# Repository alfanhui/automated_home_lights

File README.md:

# automated_home_lights
An arduino project to control 3 relay mains switches when entering a room. Controls for current ambient light, detection of direction of travel by a PIR sensor and a door magnet switch.

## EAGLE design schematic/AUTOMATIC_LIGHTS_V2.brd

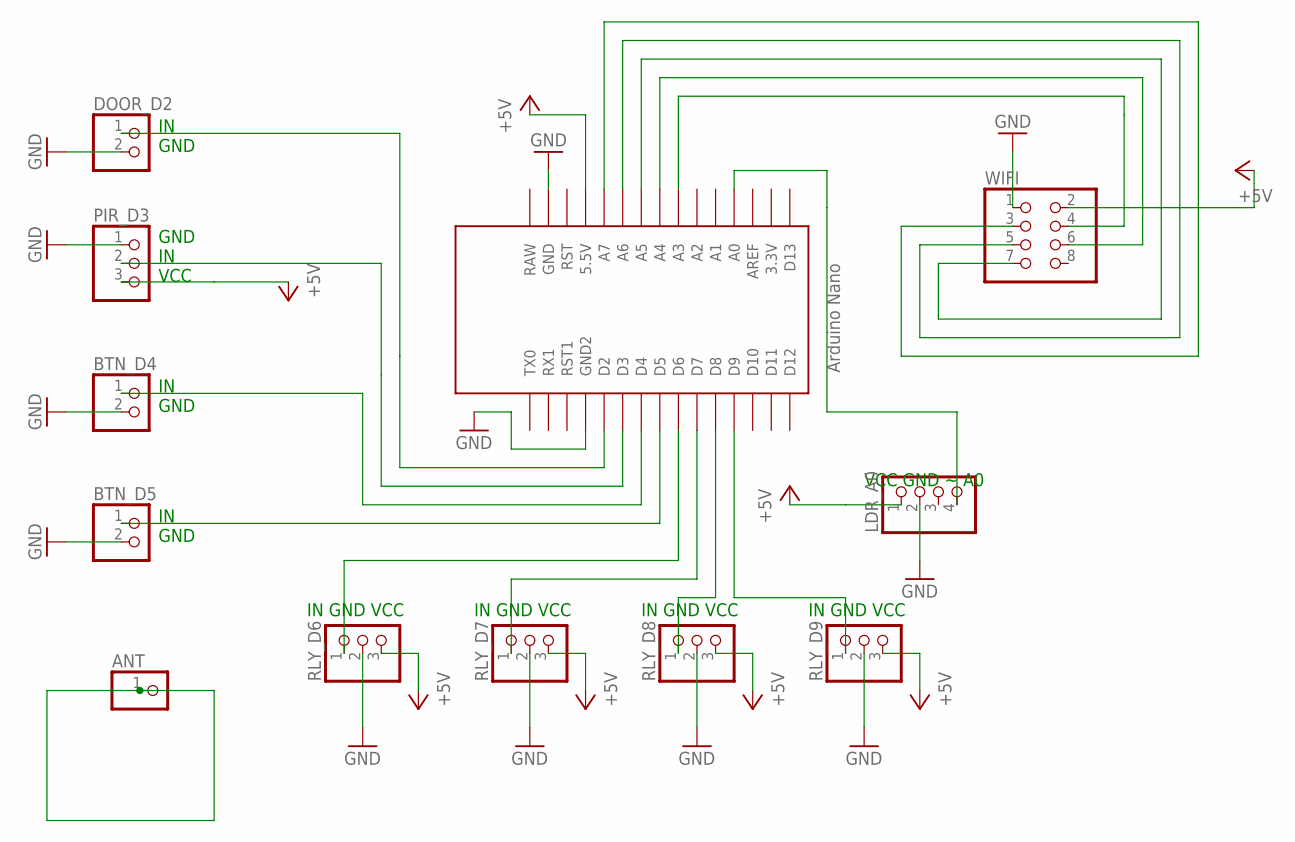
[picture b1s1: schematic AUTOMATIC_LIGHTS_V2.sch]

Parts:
ANT: PINHD-1X1; 1X01
BTN_D4, BTN_D5: PINHD-1X2; 1X02
DOOR_D2: PINHD-1X2; 1X02
LDR_A0: PINHD-1X4; 1X04
PIR_D3: PINHD-1X3; 1X03
RLY_D6, RLY_D7, RLY_D8, RLY_D9: PINHD-1X3; 1X03
U$1: NANO
WIFI: PINHD-2X4; 2X04

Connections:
+5V: LDR_A0.1, PIR_D3.3, RLY_D6.3, RLY_D7.3, RLY_D8.3, RLY_D9.3, U$1.5V (5.5V), WIFI.2
GND: BTN_D4.2, BTN_D5.2, DOOR_D2.2, LDR_A0.2, PIR_D3.1, RLY_D6.2, RLY_D7.2, RLY_D8.2, RLY_D9.2, U$1.GND, U$1.GND1 (GND2), WIFI.1
unnamed: LDR_A0.4, U$1.A0
unnamed: BTN_D4.1, U$1.D4
unnamed: BTN_D5.1, U$1.D5
unnamed: DOOR_D2.1, U$1.D2
unnamed: PIR_D3.2, U$1.D3
unnamed: RLY_D6.1, U$1.D6
unnamed: RLY_D7.1, U$1.D7
unnamed: RLY_D8.1, U$1.D8
unnamed: RLY_D9.1, U$1.D9
unnamed: U$1.A7, WIFI.3
unnamed: U$1.A6, WIFI.5
unnamed: U$1.A5, WIFI.7
unnamed: U$1.A3, WIFI.4
unnamed: U$1.A4, WIFI.6

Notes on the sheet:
IN GND VCC
IN GND
VCC GND ~ A0
GND IN VCC

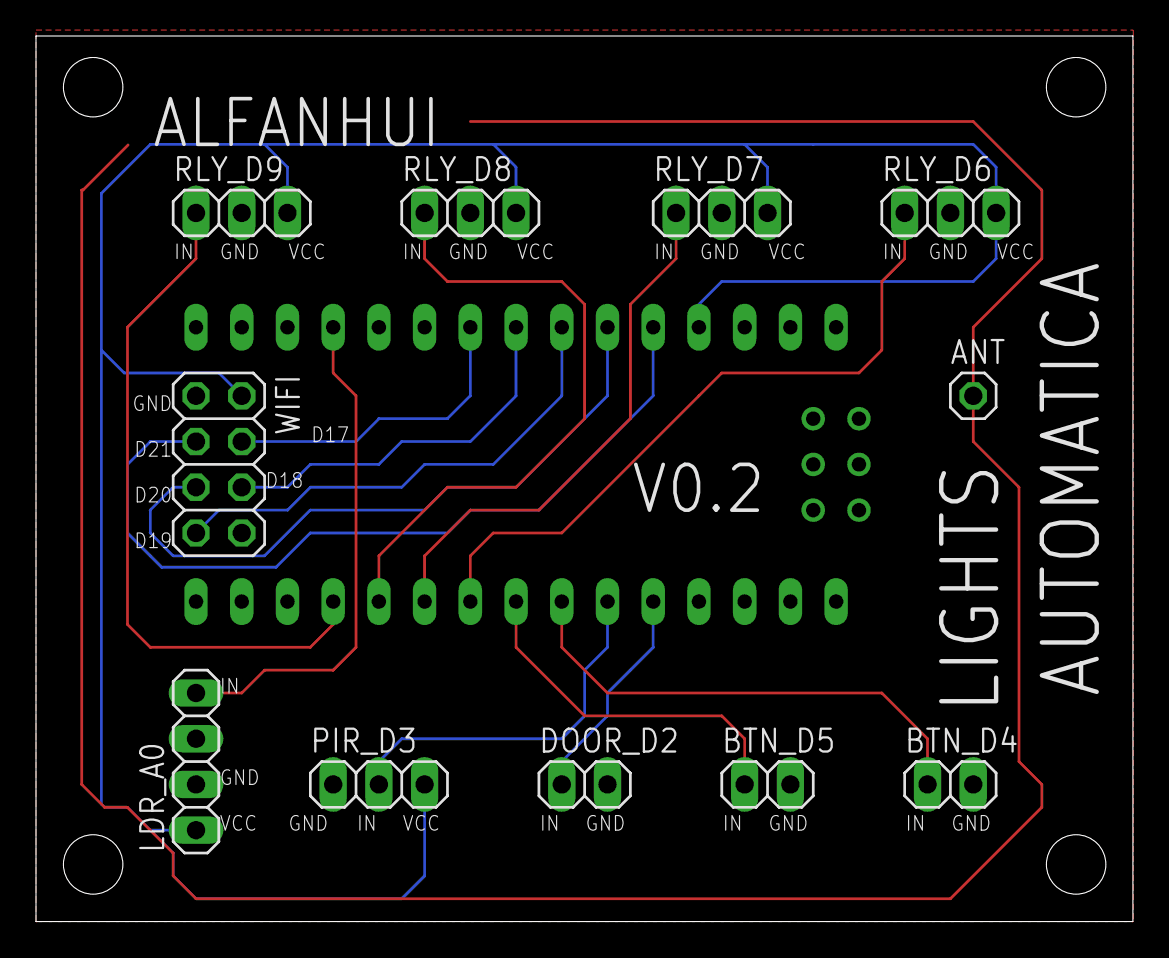
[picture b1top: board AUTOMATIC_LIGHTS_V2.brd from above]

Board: 2 copper layers, 60.9 x 49.2 mm, 12 parts (1 on the bottom side), 16 nets.

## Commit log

2018-03-14 First draft, button code untested as not currently wired.
2018-03-14 moved source to root folder
2018-03-14 gitignoring
2018-03-25 Added the button to the circuit, updated button code to work better
2018-04-09 Checked the difference between sensors when detected entered room. Should stop random house shuddering or ghosts from activating the sensor causing it to think someone has entered the room.
2018-04-14 Still coming home to lights on. Its either because the direction of travel is not confirmed and therefore gets triggered, or that the values are not reset correctly when operating master switch. Hope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
2018-06-03 Clean up some variable resets. Hopefully bug fixed re: motion not detecting someone is still in room when someone else has left (and for the lights to remain on).
2018-06-05 3 conditions added to the button. if the light has been detected within a minute of door opening(generous timing) -> reset timer (to turn on lights), or if the hasLeft timer is between 9 and 13 minut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
2018-06-11 if lights just went out, but someone is still in the room, then turn back on the chilled lighting.
2018-06-12 Previous commit was had the wrong bool value set.
2018-06-13 Refactoring, previous previous previous commit never actually worked, so hopefully when the sensor thinks I've left but then detects me in the room, it will switched to the cool chilled moood lightin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
2019-10-27 Added updated program that has TOO_DARK var and adjustments to lights turning back when they shouldn't
2020-01-17 Updated gitignore and added photo of schematic
2020-01-17 put image in readme
